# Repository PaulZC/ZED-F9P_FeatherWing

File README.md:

# ZED-F9P_FeatherWing

An **untested** GNSS FeatherWing incorporating the dual-band (L1 + L2) [u-blox ZED-F9P](https://www.u-blox.com/en/product/zed-f9p-module)

If you need access to the ZED-F9P's USB port, check out the [ZED-F9P_FeatherWing_USB](https://github.com/PaulZC/ZED-F9P_FeatherWing_USB)

Based extensively on the [Adafruit Ultimate GPS FeatherWing](https://www.adafruit.com/product/3133) and the
[SparkFun GPS-RTK2 Board](https://www.sparkfun.com/products/15136)

The Eagle files are available in the [Eagle folder](https://github.com/PaulZC/ZED-F9P_FeatherWing/tree/master/Eagle)

The schematic is available [here](https://github.com/PaulZC/ZED-F9P_FeatherWing/blob/master/img/Schematic.PNG)

The BOM is available [here](https://github.com/PaulZC/ZED-F9P_FeatherWing/blob/master/BOM.pdf)

PCB thickness should be 0.8mm: see the microstrip calculations on the [SparkFun schematic](https://cdn.sparkfun.com/assets/9/a/0/0/a/Qwiic_GPS-RTK2_-_ublox_ZED-F9P.pdf)

## Acknowledgements

This project would not have been possible without the open source designs kindly provided by both Adafruit and SparkFun. Their work is gratefully acknowledged.

Adafruit invests time and resources providing this open source design, please support Adafruit and open-source hardware by purchasing products from Adafruit!

## Licence

This project is distributed under a Creative Commons Attribution + Share-alike (BY-SA) licence.
Please refer to section 5 of the licence for the "Disclaimer of Warranties and Limitation of Liability".

Enjoy!

**_Paul_**

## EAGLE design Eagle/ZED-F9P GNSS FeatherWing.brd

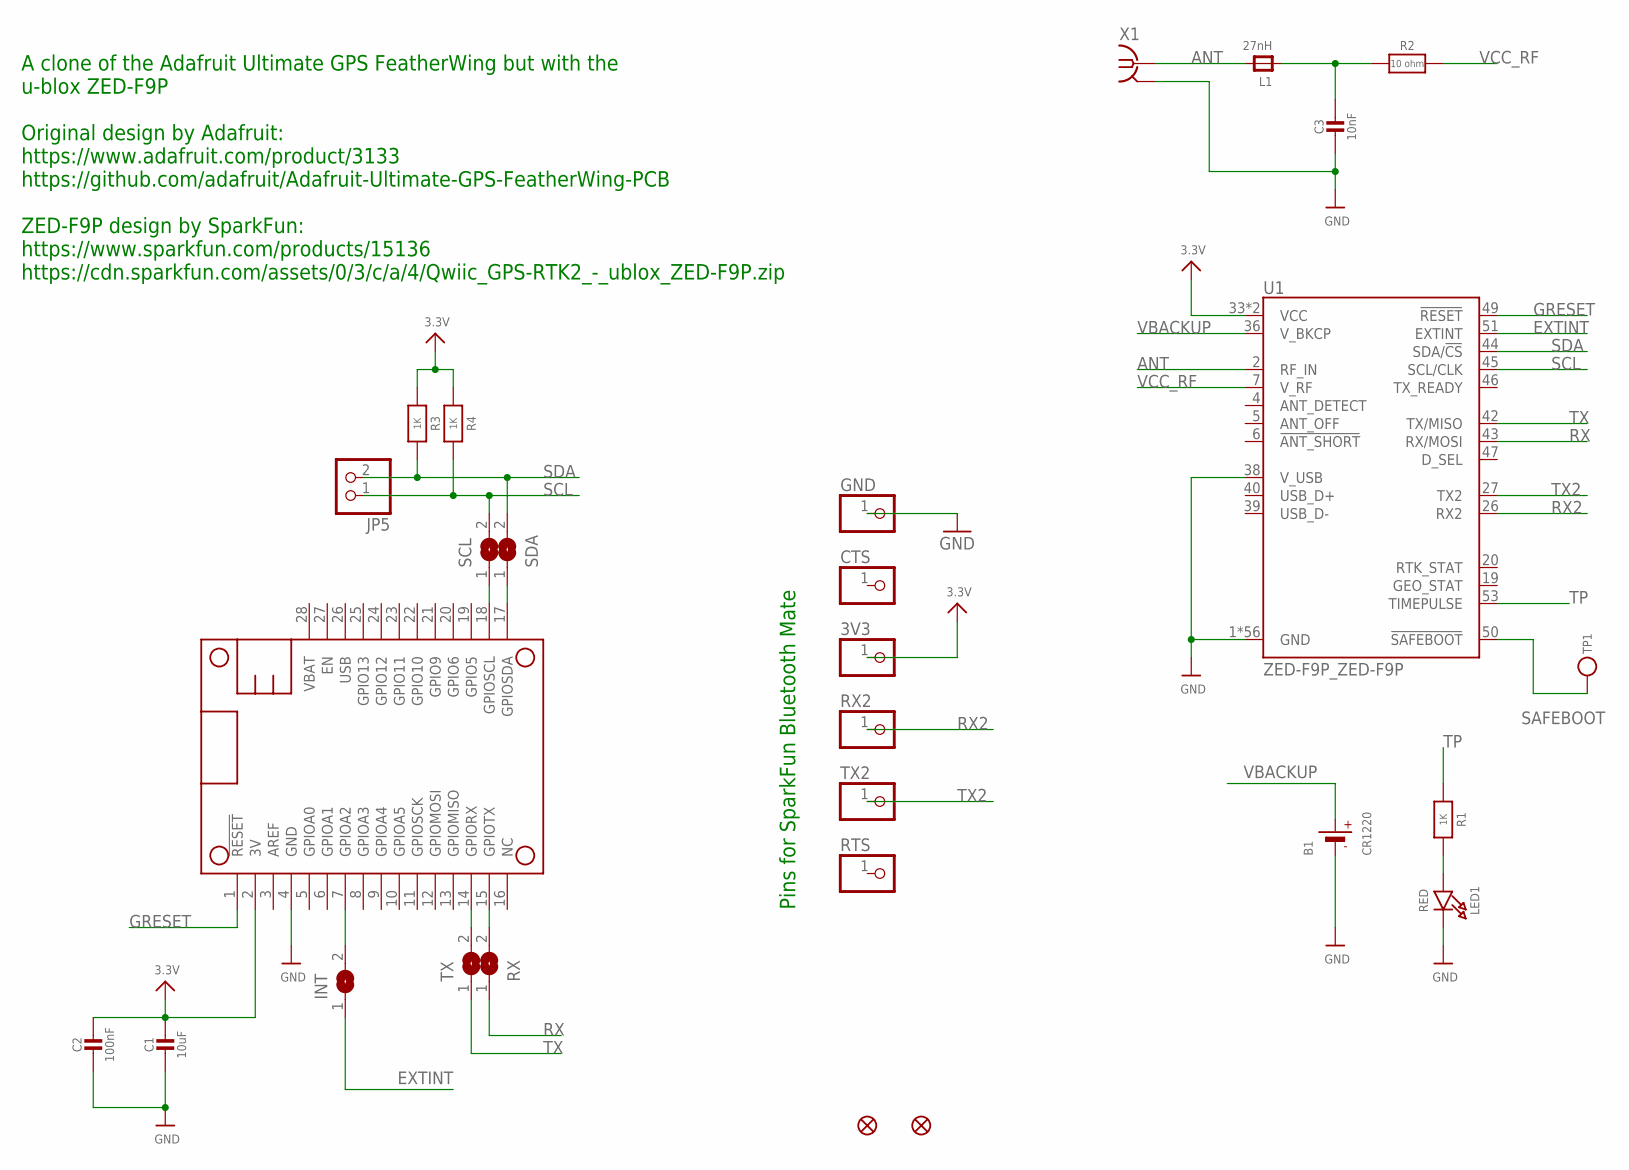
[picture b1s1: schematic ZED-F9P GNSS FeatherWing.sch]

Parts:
3V3: PINHD-1X1; 1X01
B1: CR1220; CR1220-2
C1: 10uF; 0805-NO
C2: 100nF; 0805-NO
C3: 10nF; 0805-NO
CTS: PINHD-1X1; 1X01
FID1, FID2: FIDUCIAL""; FIDUCIAL_1MM
GND: PINHD-1X1; 1X01
INT: SOLDERJUMPERCLOSED; SOLDERJUMPER_CLOSEDWIRE
JP5: HEADER-1X2ROUND; 1X02_ROUND
L1: 27nH; 0805-NO
LED1: RED; CHIPLED_0805_NOOUTLINE
MS1: MICROBUILDER_FEATHERWINGMICROBUILDER_FEATHERWING_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; MICROBUILDER_FEATHERWING_HOLES
R1, R3, R4: 1K; 0603-NO
R2: 10 ohm; 0805-NO
RTS: PINHD-1X1; 1X01
RX: SOLDERJUMPERCLOSED; SOLDERJUMPER_CLOSEDWIRE
RX2: PINHD-1X1; 1X01
SCL: SOLDERJUMPERCLOSED; SOLDERJUMPER_CLOSEDWIRE
SDA: SOLDERJUMPERCLOSED; SOLDERJUMPER_CLOSEDWIRE
TP1: TESTPOINTROUND1.5MM; TESTPOINT_ROUND_1.5MM
TX: SOLDERJUMPERCLOSED; SOLDERJUMPER_CLOSEDWIRE
TX2: PINHD-1X1; 1X01
U1: ZED-F9P_ZED-F9P
X1: SMA-142-0711-821/826; J502-ND-142-0711-821/826

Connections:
3.3V: 3V3.1, C1.1, C2.1, MS1.2 (3V), R3.1, R4.1, U1.33 (VCC), U1.34 (VCC)
ANT: L1.2, U1.2 (RF_IN), X1.1
EXTINT: INT.1, U1.51 (EXTINT)
GND: B1.-, C1.2, C2.2, C3.2, GND.1, LED1.C, MS1.4 (GND), U1.1 (GND), U1.3 (GND), U1.12 (GND), U1.14 (GND), U1.32 (GND), U1.37 (GND), U1.38 (V_USB), U1.41 (GND), U1.48 (GND), U1.55 (GND), U1.56 (GND), U1.57 (GND), U1.58 (GND), U1.59 (GND), U1.60 (GND), U1.61 (GND), U1.62 (GND), U1.63 (GND), U1.64 (GND), U1.65 (GND), U1.66 (GND), U1.67 (GND), U1.68 (GND), U1.69 (GND), U1.70 (GND), U1.71 (GND), U1.72 (GND), U1.73 (GND), U1.74 (GND), U1.75 (GND), U1.76 (GND), U1.77 (GND), U1.78 (GND), U1.79 (GND), U1.80 (GND), U1.81 (GND), U1.82 (GND), U1.83 (GND), U1.84 (GND), U1.85 (GND), U1.86 (GND), U1.87 (GND), U1.88 (GND), U1.89 (GND), U1.90 (GND), U1.91 (GND), U1.92 (GND), U1.93 (GND), U1.94 (GND), U1.95 (GND), U1.96 (GND), U1.97 (GND), U1.98 (GND), U1.99 (GND), U1.100 (GND), U1.101 (GND), U1.102 (GND), X1.G@1 (2), X1.G@2 (2), X1.G@3 (2), X1.G@4 (2)
GRESET: MS1.1 (!RESET), U1.49 (!RESET!)
unnamed: MS1.18 (GPIOSCL), SCL.1
unnamed: LED1.A, R1.2
unnamed: MS1.17 (GPIOSDA), SDA.1
unnamed: C3.1, L1.1, R2.1
unnamed: MS1.14 (GPIORX), TX.2
unnamed: MS1.15 (GPIOTX), RX.2
unnamed: INT.2, MS1.7 (GPIOA2)
RX: RX.1, U1.43 (RX/MOSI)
RX2: RX2.1, U1.26 (RX2)
SAFEBOOT: TP1.P$1, U1.50 (!SAFEBOOT!)
SCL: JP5.1, R4.2, SCL.2, U1.45 (SCL/CLK)
SDA: JP5.2, R3.2, SDA.2, U1.44 (SDA/!CS!)
TP: R1.1, U1.53 (TIMEPULSE)
TX: TX.1, U1.42 (TX/MISO)
TX2: TX2.1, U1.27 (TX2)
VBACKUP: B1.+, U1.36 (V_BKCP)
VCC_RF: R2.2, U1.7 (V_RF)

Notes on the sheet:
A clone of the Adafruit Ultimate GPS FeatherWing but with the u-blox ZED-F9P Original design by Adafruit: https://www.adafruit.com/product/3133 https://github.com/adafruit/Adafruit-Ultimate-GPS-FeatherWing-PCB ZED-F9P design by SparkFun: https://www.sparkfun.com/products/15136 https://cdn.sparkfun.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
Pins for SparkFun Bluetooth Mate

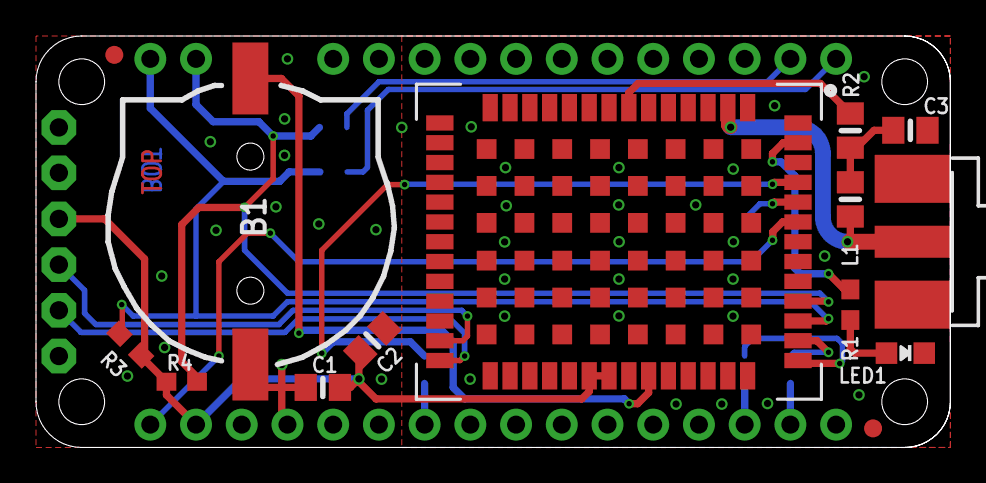
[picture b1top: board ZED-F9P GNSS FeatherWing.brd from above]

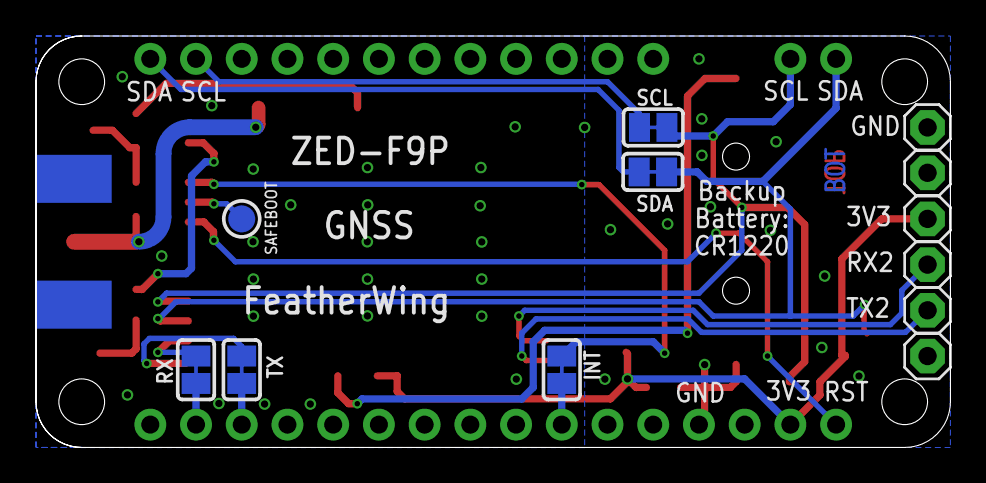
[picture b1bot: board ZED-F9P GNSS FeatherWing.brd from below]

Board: 2 copper layers, 50.8 x 22.9 mm, 28 parts (12 on the bottom side), 22 nets.

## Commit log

2019-06-01 Resized the images
2019-06-01 Added the PCB thickness
